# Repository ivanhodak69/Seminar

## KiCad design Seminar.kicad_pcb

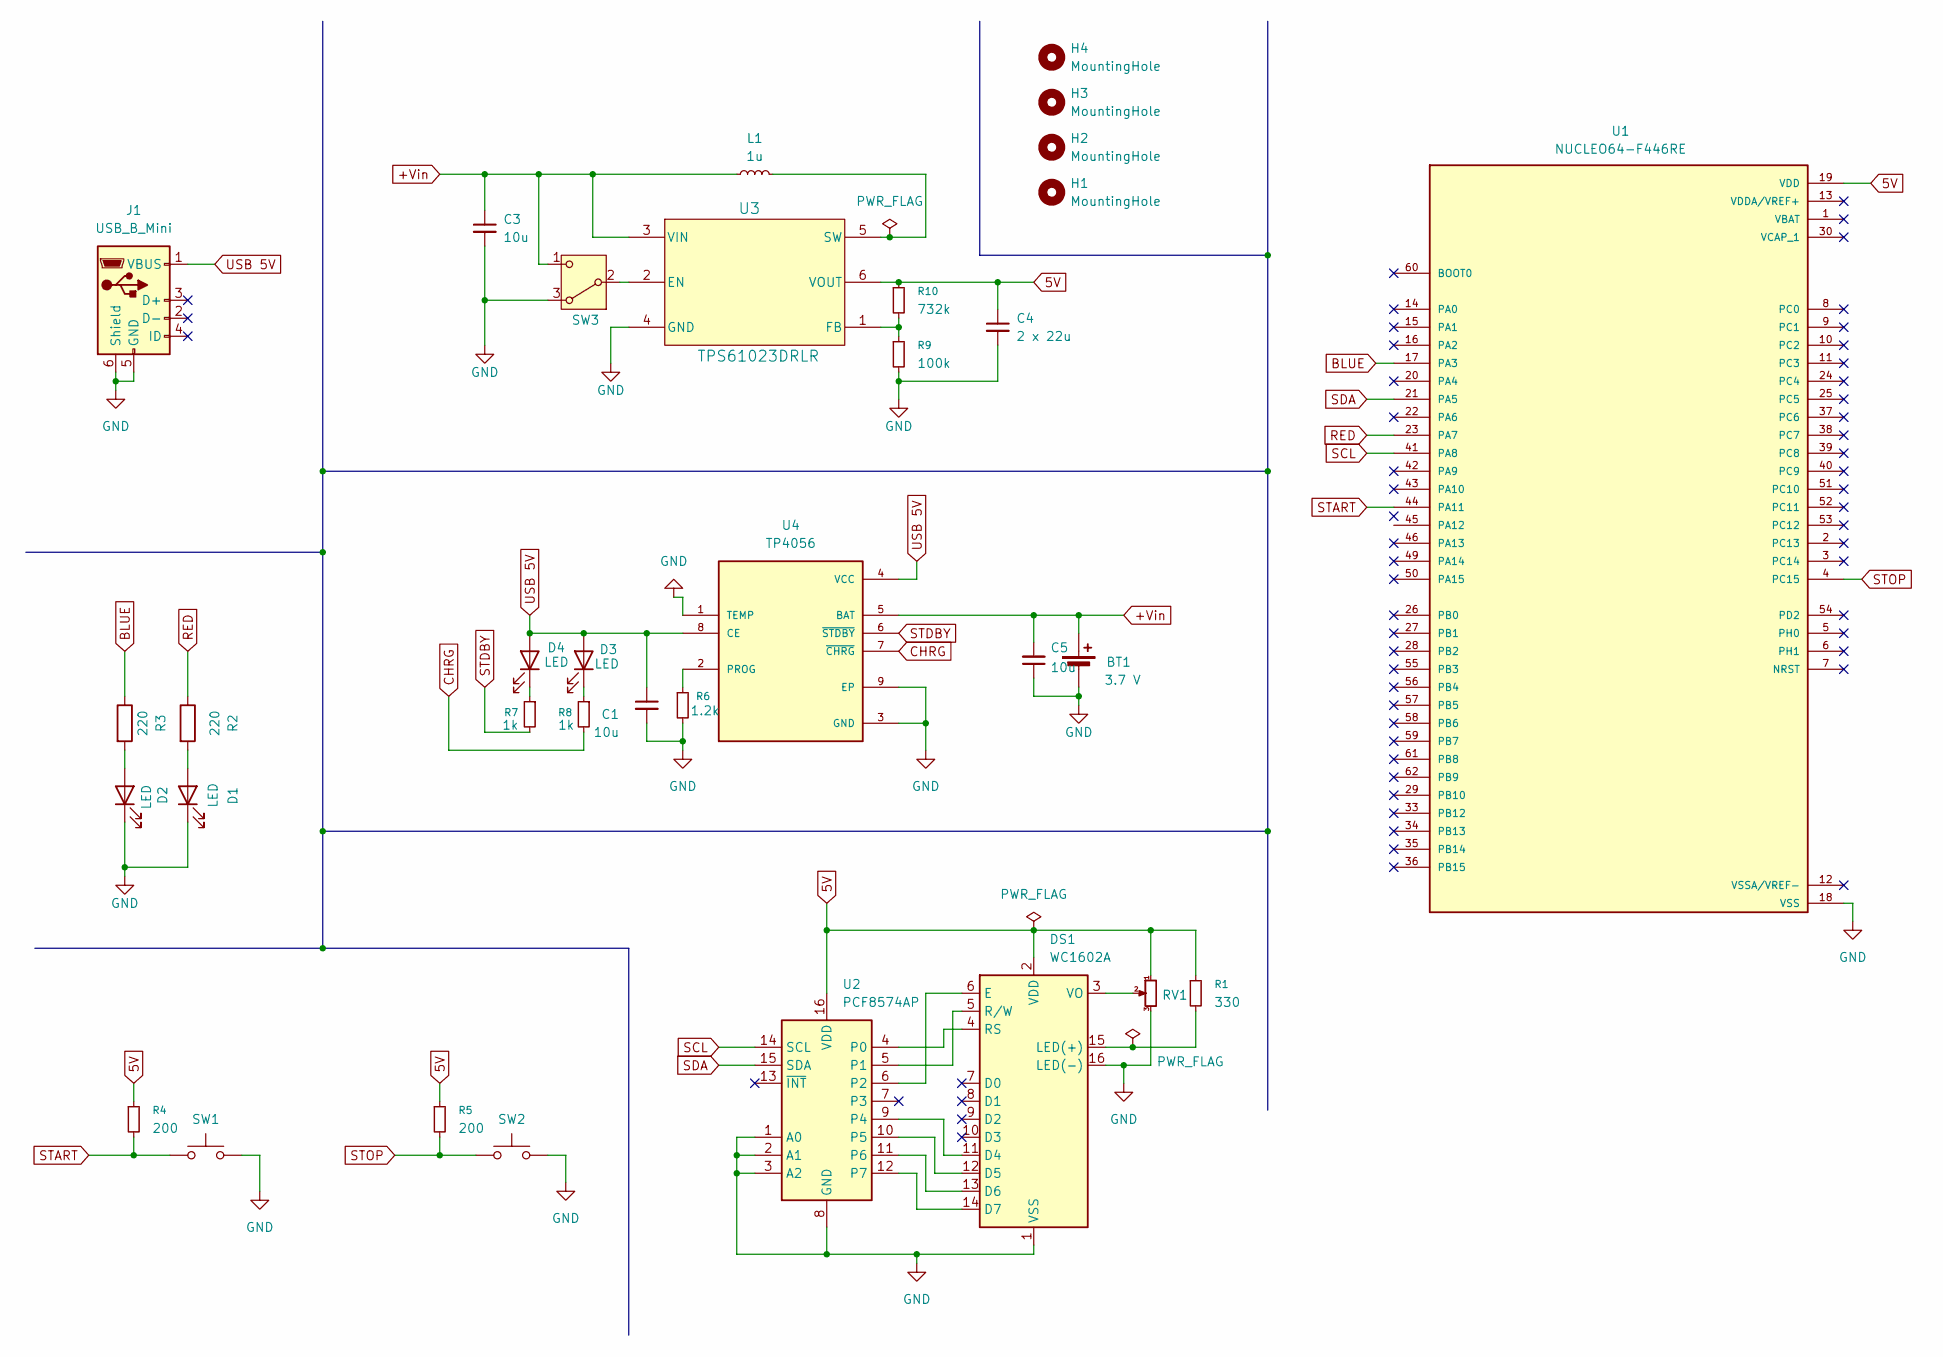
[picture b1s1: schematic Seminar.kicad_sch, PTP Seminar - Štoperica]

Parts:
BT1: 3.7 V; BatteryHolder_Keystone_1042_1x18650; Manufacturer part number 18650-2200mAh-3.7V
C1, C3, C5: 10u; C_1206_3216Metric_Pad1.33x1.80mm_HandSolder; Manufacturer part number CL31A106KBHNNNE
C4: 2 x 22u; CP_Radial_D5.0mm_P2.00mm; Manufacturer part number EWH1EM220D11OT
D1, D2, D3, D4: LED; LED_D5.0mm; Manufacturer part number TLH540
DS1: WC1602A; Manufacturer part number WC1602B0SGW6B-A1
H1, H2, H3, H4: MountingHole; MountingHole_5.5mm
J1: USB_B_Mini; USB_Mini-B_Lumberg_2486_01_Horizontal; Manufacturer part number 2486-01
L1: 1u; L_Radial_D7.2mm_P3.00mm_Murata_1700; Manufacturer part number COIL0608-0.33
R1: 330; R_1206_3216Metric_Pad1.30x1.75mm_HandSolder; Manufacturer part number 1206S4F2001T5E
R2, R3: 220; R_1206_3216Metric_Pad1.30x1.75mm_HandSolder; Manufacturer part number 1206S4F2001T5E
R4, R5: 200; R_1206_3216Metric_Pad1.30x1.75mm_HandSolder; Manufacturer part number 1206S4F2001T5E
R6: 1.2k; R_1206_3216Metric_Pad1.30x1.75mm_HandSolder; Manufacturer part number 1206S4F2001T5E
R7, R8: 1k; R_1206_3216Metric_Pad1.30x1.75mm_HandSolder; Manufacturer part number 1206S4F2001T5E
R9: 100k; R_1206_3216Metric_Pad1.30x1.75mm_HandSolder; Manufacturer part number 1206S4J0473T5E
R10: 732k; R_1206_3216Metric_Pad1.30x1.75mm_HandSolder; Manufacturer part number 1206S4J0473T5E
RV1: R_Potentiometer_Small; Potentiometer_Bourns_3299Y_Vertical; Manufacturer part number PDB181-GTR03-504A2
SW1, SW2: SW_Push; SW_PUSH_6mm_H4.3mm; Manufacturer part number TACT-64N-F
SW3: SPDT; SW_Slide_SPDT_Straight_CK_OS102011MS2Q; Manufacturer part number CAS - 120TB1
U1: NUCLEO64-F446RE; QFP50P1200X1200X160-64N; Manufacturer part number STM32F446RET6
U2: PCF8574AP; DIP-16_W7.62mm; Manufacturer part number PCF8574AP,112
U3: TPS61023DRLR; SOT563-ORI; Manufacturer part number TPS61023
U4: TP4056; SOP127P600X175-9N; Manufacturer part number TP4056

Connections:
5V: C4.1, DS1.2 (VDD), R1.1, R4.1, R5.1, R10.1, RV1.1, U1.19 (VDD), U1.32 (VDD), U1.48 (VDD), U1.64 (VDD), U2.16 (VDD), U3.6 (VOUT)
+Vin: BT1.1 (+), C3.1, C5.2, L1.1, SW3.1 (C), U3.3 (VIN), U4.5 (BAT)
BLUE: R3.1, U1.17 (PA3)
CHRG: R8.2, U4.7 (~CHRG)
GND: BT1.2 (-), C1.2, C3.2, C4.2, C5.1, D1.1 (K), D2.1 (K), DS1.1 (VSS), DS1.16 (LED(-)), J1.5 (GND), J1.6 (Shield), R6.2, R9.2, RV1.3, SW1.2, SW2.2, SW3.3 (A), U1.18 (VSS), U1.31 (VSS), U1.47 (VSS), U1.63 (VSS), U2.1 (A0), U2.2 (A1), U2.3 (A2), U2.8 (GND), U3.4 (GND), U4.1 (TEMP), U4.3 (GND), U4.9 (EP)
unnamed: D1.2 (A), R2.2
unnamed: D2.2 (A), R3.2
unnamed: D3.1 (K), R8.1
unnamed: D4.1 (K), R7.1
unnamed: DS1.11 (D4), U2.9 (P4)
unnamed: DS1.12 (D5), U2.10 (P5)
unnamed: DS1.13 (D6), U2.11 (P6)
unnamed: DS1.14 (D7), U2.12 (P7)
unnamed: DS1.6 (E), U2.6 (P2)
unnamed: DS1.15 (LED(+)), R1.2
unnamed: DS1.4 (RS), U2.4 (P0)
unnamed: DS1.5 (R/W), U2.5 (P1)
unnamed: DS1.3 (VO), RV1.2
unnamed: SW3.2 (B), U3.2 (EN)
unnamed: R9.1, R10.2, U3.1 (FB)
unnamed: L1.2, U3.5 (SW)
unnamed: R6.1, U4.2 (PROG)
RED: R2.1, U1.23 (PA7)
SCL: U1.41 (PA8), U2.14 (SCL)
SDA: U1.21 (PA5), U2.15 (SDA)
START: R4.2, SW1.1, U1.44 (PA11)
STDBY: R7.2, U4.6 (~STDBY)
STOP: R5.2, SW2.1, U1.4 (PC15)
USB 5V: C1.1, D3.2 (A), D4.2 (A), J1.1 (VBUS), U4.4 (VCC), U4.8 (CE)

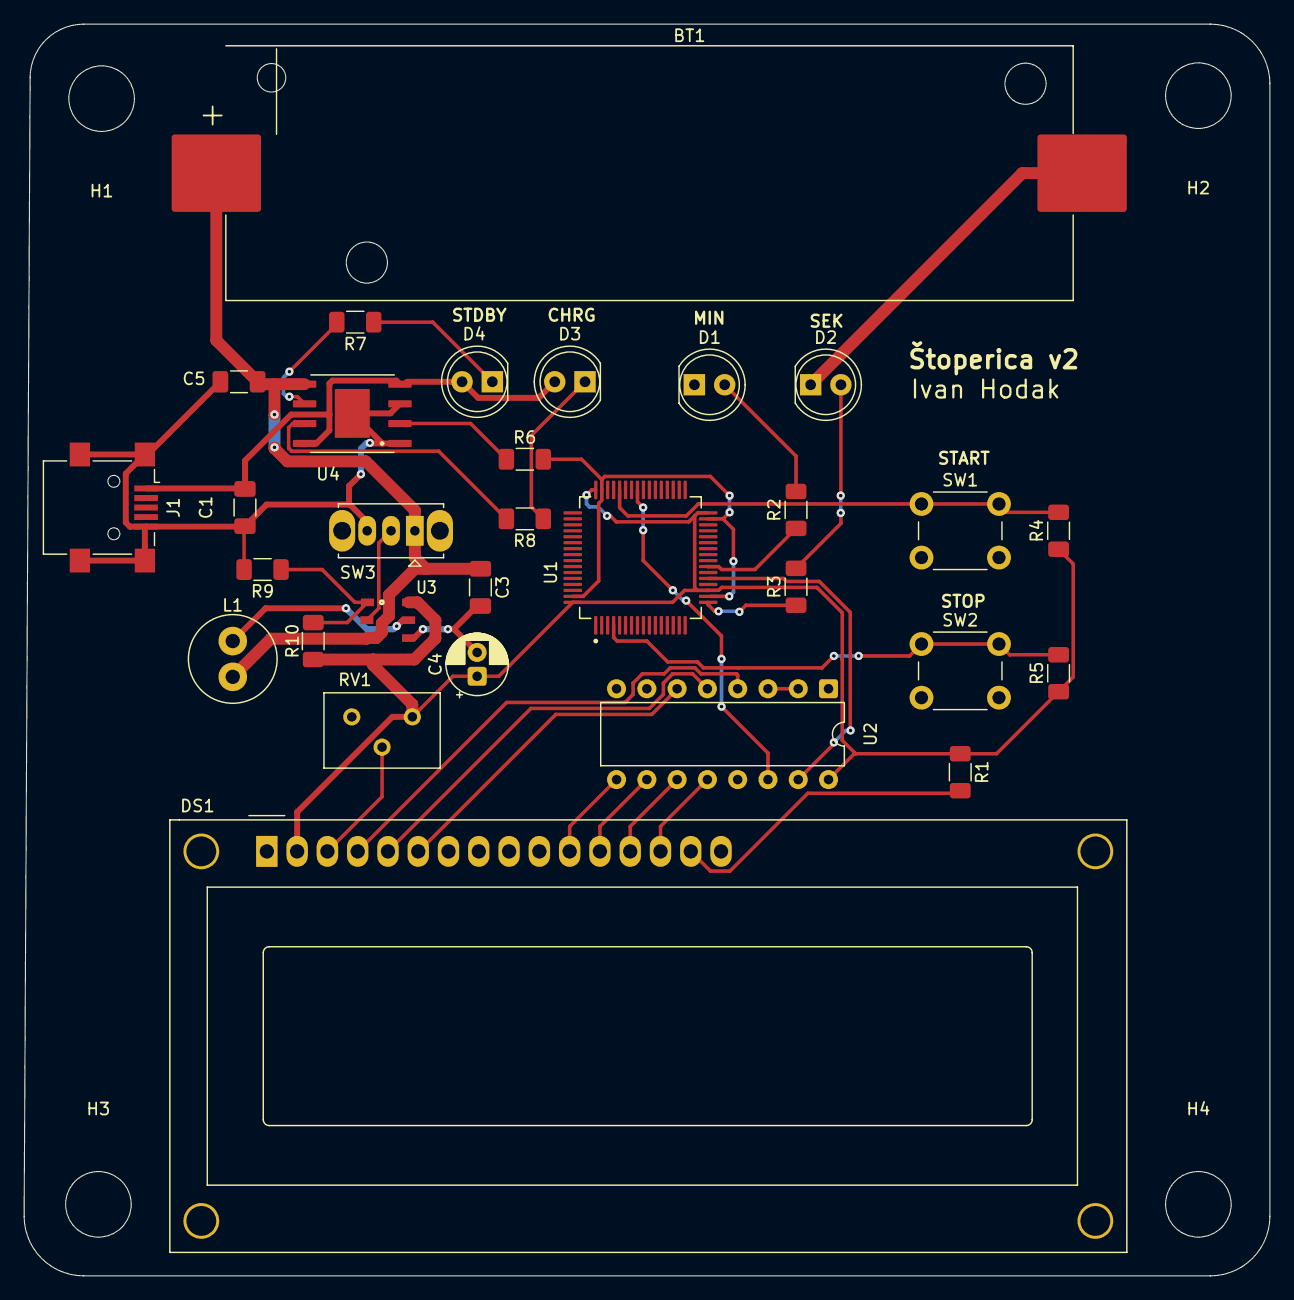
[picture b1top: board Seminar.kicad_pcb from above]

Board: 2 copper layers, 104.5 x 105.0 mm, 34 parts (0 on the bottom side), 29 nets.

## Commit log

2025-11-29 PCB update
2025-12-07 Update Seminar 7.12.
2025-12-07 Update Seminar 7.12. dva
2025-12-07 7.12. tri
2025-12-10 Baterija i Step up
2025-12-11 Mucenje
2025-12-12 update 3d model
2025-12-17 uprdejt
2025-12-26 Word
2026-01-14 Finito
2026-01-25 dorada
2026-02-06 Final
